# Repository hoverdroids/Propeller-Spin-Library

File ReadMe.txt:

The files in this library are derived from file in OBEX. Some have been modified to different degrees and all have
been verified not to conflict with other files in the library. It's for these reasons that they have been given the
HoverDroids prefix.

Our team at HoverDroids isn't simply trying to copy the great code written by other authors, which should be clear by
the fact we've kept all previous authors' names, credits, and equivalent licenses in each file.

Finally, our objective is to create a better environment for coding the Parallax Propeller in the Spin and PASM languages,
so that Makers can spend less time coding the Propeller and more time integrating it into their projects.

If you have any questions, comments, or requests, please contact me personally.

Sincerely,
Chris Sprague
HoverDroids.com
HoverDroids@gmail.com

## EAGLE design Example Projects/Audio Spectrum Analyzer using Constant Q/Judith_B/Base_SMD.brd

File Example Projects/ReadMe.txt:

Do not simply throw an unzipped project into this folder! Instead, move dependencies to
the category folders so that other projects can use them. This allows us to see how the different
elements fit into the project so that we can grab just the components and not the integration.

If there are two files that have the same name, compare the files. If identical, delete the duplicate.
If the files are not the same, either integrate the duplicate into the current file or rename the duplicate
and update the project dependencies. This is because files cannot have the same name when using Brad's Spin Tool

If you merge the files, it's up to you to ensure there is no conflict between the old code and new.

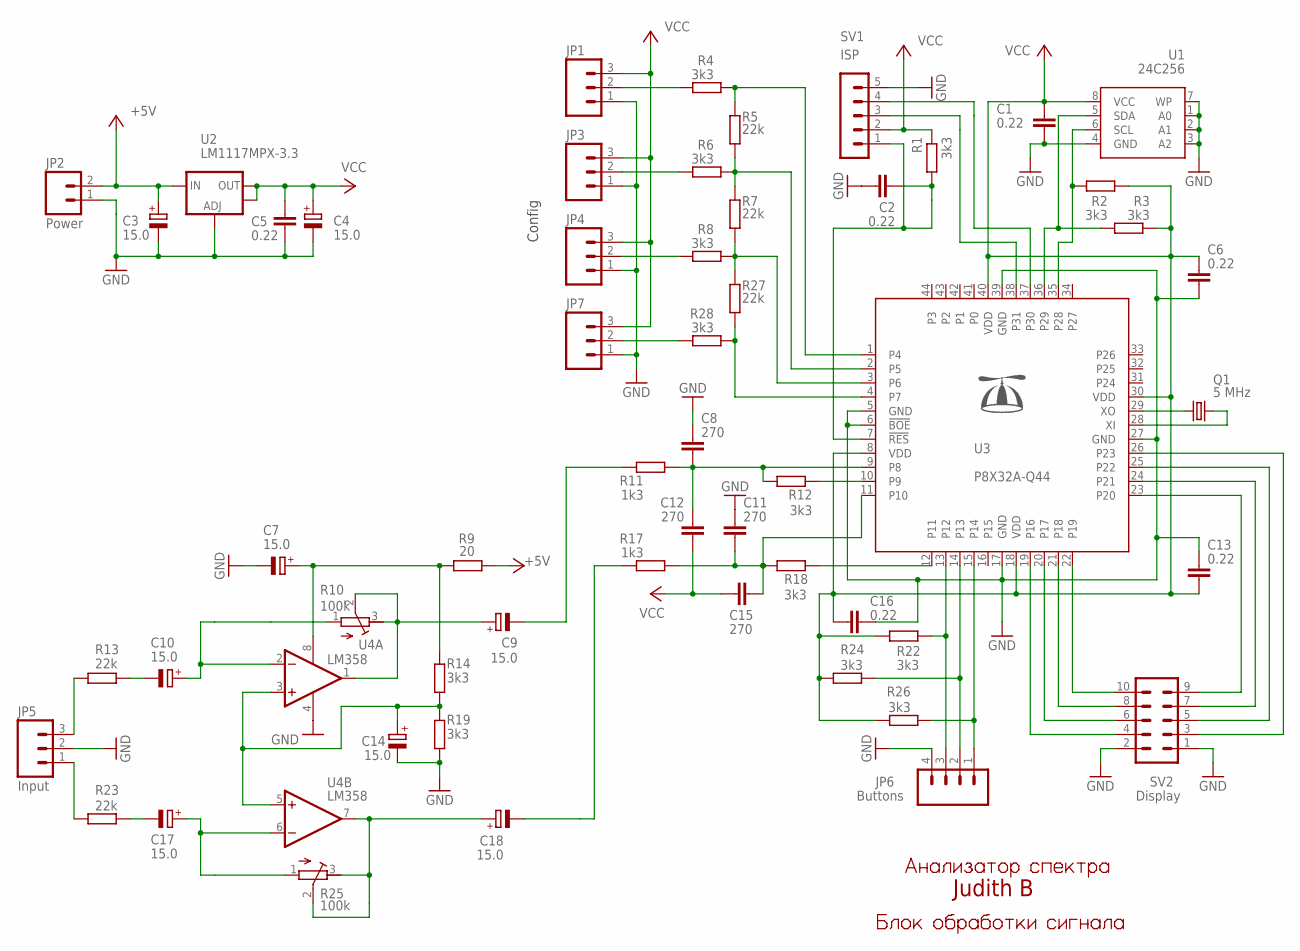
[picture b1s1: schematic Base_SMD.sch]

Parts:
C1, C2, C5, C6, C13, C16: 0.22; C0805
C3, C4, C7, C9, C10, C14, C17, C18: 15.0; SMC_B
C8, C11, C12, C15: 270; C0805
JP1, JP3, JP4, JP7: M03PTH; 1X03
JP2: Power; 1X02
JP5: Input; 1X03
JP6: Buttons; 1X04
Q1: 5 MHz; HC49/S
R1, R2, R3, R4, R6, R8, R12, R14, R18, R19, R22, R24, R26, R28: 3k3; R0805
R5, R7, R13, R23, R27: 22k; R0805
R9: 20; R0805
R10, R25: 100k; RTRIM3296W
R11, R17: 1k3; R0805
SV1: ISP; MA05-1
SV2: Display; MA05-2
U1: 24C256; SO08
U2: LM1117MPX-3.3; SOT223
U3: P8X32A-Q44; SQFP-S-10X10-44
U4: LM358; SO08

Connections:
+5V: C3.+, JP2.2, R9.1, U2.3 (IN)
GND: C1.2, C2.1, C3.-, C4.-, C5.1, C6.2, C7.-, C8.1, C11.1, C13.1, C14.-, C16.2, JP1.1, JP2.1, JP3.1, JP4.1, JP5.2, JP6.4, JP7.1, R19.2, SV1.5, SV2.1, SV2.2, U1.1 (A0), U1.2 (A1), U1.3 (A2), U1.4 (GND), U1.7 (WP), U2.1 (ADJ), U3.5 (GND), U3.6 (!BOE), U3.17 (GND), U3.27 (GND), U3.39 (GND), U4.4 (V-)
unnamed: C18.-, R17.2
unnamed: C9.-, R11.2
unnamed: Q1.2, U3.28 (XI)
unnamed: Q1.1, U3.29 (XO)
unnamed: C8.2, C12.2, R11.1, R12.2, U3.9 (P8)
unnamed: R12.1, U3.10 (P9)
unnamed: SV1.4, U3.37 (P30)
unnamed: SV1.3, U3.38 (P31)
unnamed: R2.2, U1.6 (SCL), U3.35 (P28)
unnamed: C17.-, R23.2
unnamed: C10.-, R13.2
unnamed: C18.+, R25.2 (S), R25.3 (A), U4.7 (OUT)
unnamed: C9.+, R10.2 (S), R10.3 (A), U4.1 (OUT)
unnamed: R3.2, U1.5 (SDA), U3.36 (P29)
unnamed: C11.2, C15.2, R17.1, R18.2, U3.11 (P10)
unnamed: JP5.1, R23.1
unnamed: JP5.3, R13.1
unnamed: C10.+, R10.1 (E), U4.2 (-IN)
unnamed: R18.1, U3.12 (P11)
unnamed: C7.+, R9.2, R14.1, U4.8 (V+)
unnamed: JP6.1, R26.1, U3.15 (P14)
unnamed: JP6.2, R24.1, U3.14 (P13)
unnamed: JP6.3, R22.1, U3.13 (P12)
unnamed: R5.2, R6.1, R7.1, U3.2 (P5)
unnamed: SV2.4, U3.19 (P16)
unnamed: SV2.6, U3.20 (P17)
unnamed: SV2.8, U3.21 (P18)
unnamed: SV2.10, U3.22 (P19)
unnamed: SV2.9, U3.23 (P20)
unnamed: SV2.7, U3.24 (P21)
unnamed: SV2.5, U3.25 (P22)
unnamed: SV2.3, U3.26 (P23)
unnamed: R7.2, R8.1, R27.1, U3.3 (P6)
unnamed: R4.1, R5.1, U3.1 (P4)
unnamed: JP4.2, R8.2
unnamed: JP3.2, R6.2
unnamed: JP1.2, R4.2
unnamed: C2.2, R1.2, SV1.1, U3.7 (!RES)
unnamed: C17.+, R25.1 (E), U4.6 (-IN)
unnamed: R27.2, R28.1, U3.4 (P7)
unnamed: C14.+, R14.2, R19.1, U4.3 (+IN), U4.5 (+IN)
unnamed: JP7.2, R28.2
VCC: C1.1, C4.+, C5.2, C6.1, C12.1, C13.2, C15.1, C16.1, JP1.3, JP3.3, JP4.3, JP7.3, R1.1, R2.1, R3.1, R22.2, R24.2, R26.2, SV1.2, U1.8 (VCC), U2.2 (OUT), U2.4 (OUT), U3.8 (VDD), U3.18 (VDD), U3.30 (VDD), U3.40 (VDD)

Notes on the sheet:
Config
Judith B

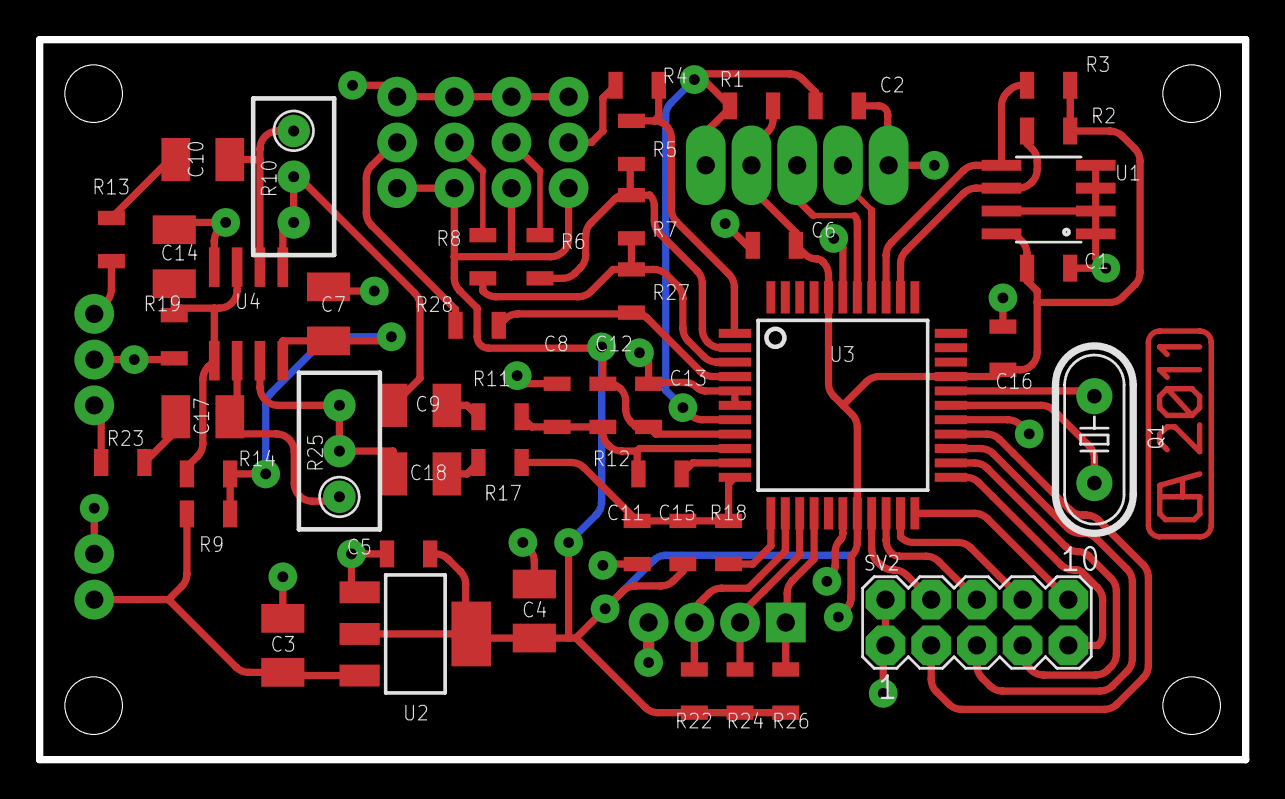
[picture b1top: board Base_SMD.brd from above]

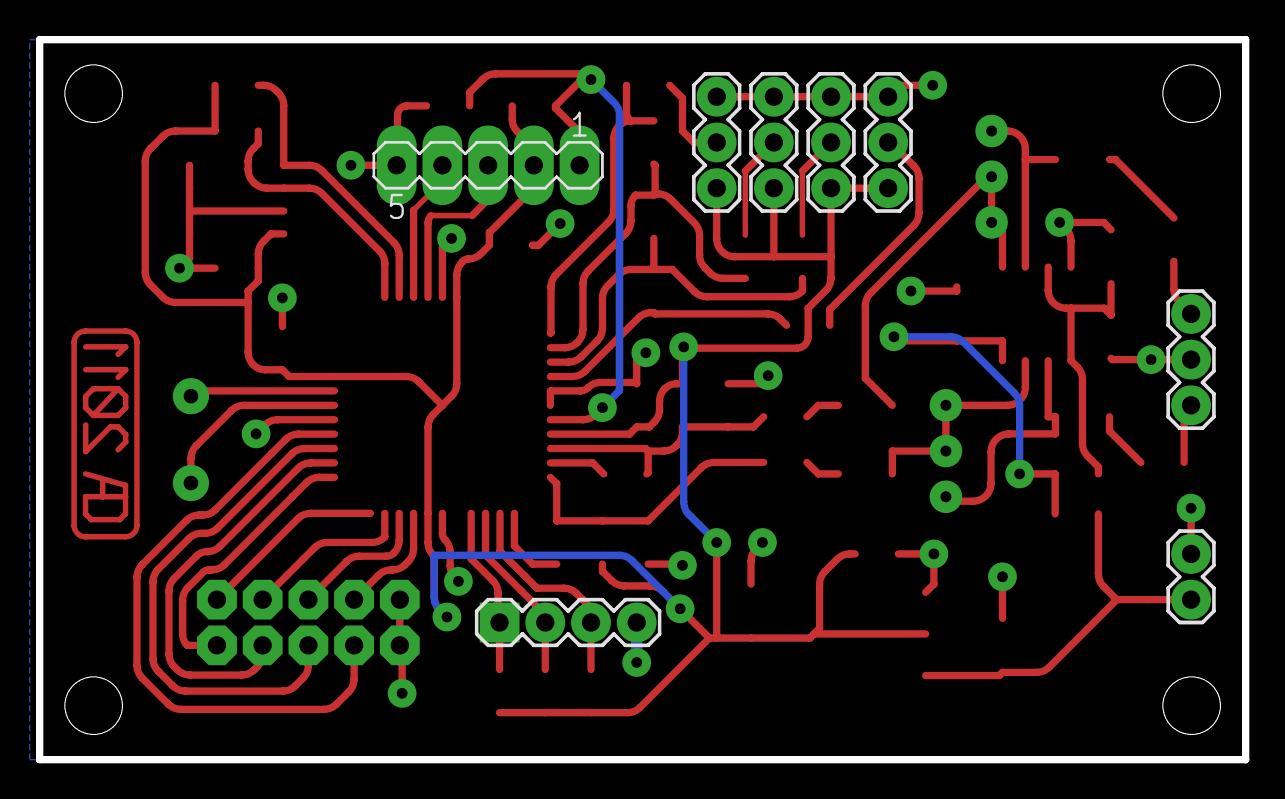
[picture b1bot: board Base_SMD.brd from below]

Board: 2 copper layers, 67.0 x 40.0 mm, 56 parts (8 on the bottom side), 45 nets.

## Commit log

2016-08-10 Serial Router is now using HoverDroids files instead of older files, without showing gibberish.
2016-08-10 About to move lots of lines of code around in Serial Router, so here's a safe restore point
2016-08-11 Finished breaking apart the serial router into smaller pieces. Developer can now update project-specific files in a single simplified file where the rest of their code lives.
2019-01-01 Added and organized code from http://obex.parallax.com/object/413 because the serial router code derived from it
2019-01-01 Moved numerous serial comms spin files to the library after verifying and sorting. Moved all Serial Router files and removed all duplicates.
2019-01-08 Added LED and String OBEX objects
2019-01-08 String functions have been moved from OBEX objects to (HoverDroids) String Utils. I still need to merge functions that provide the same functionality, standardize the notes, and ensure it compiles.
2019-01-10 All but old AIQB code has been sorted. But, lots will be broken because of renaming and broken filepaths
2019-01-10 Merged all of the files from Code->Spin into the library. Everything is still broken though ;P
2019-01-10 Moved Help/Info/etc and all non code out of the library. Examples are now in their own repository
2019-01-11 Added HoverDroids versions of SerialPortBankN, with more intuitive names, standard headers, etc.
2019-01-13 Copied constants and functions from FullDuplexSerialPlus into SerialPorts 132Byte Banks0-3 and tested the sending functions in a demo by the same name. Strings appear to send correctly but not sure a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
